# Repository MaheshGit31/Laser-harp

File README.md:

# Laser-harp

An 8-string laser harp. Break a laser beam, and it plays a note. it shows up as a usb midi device, so it works with any daw or synth on your laptop.

## how it works
 
8 red lasers on the base shine straight up at 8 phototransistors on a bar on top of them. when your hand breaks a beam, that string's signal flips and the esp32 sends a midi note over usb. a neopixel under each string lights up while you play it.

## frame idea
 
a wood or 3d-printed arch holds the bar, hollow curved side pillars carry the cable, and a chunky base case holds the base pcb. none of this is built yet.

## images

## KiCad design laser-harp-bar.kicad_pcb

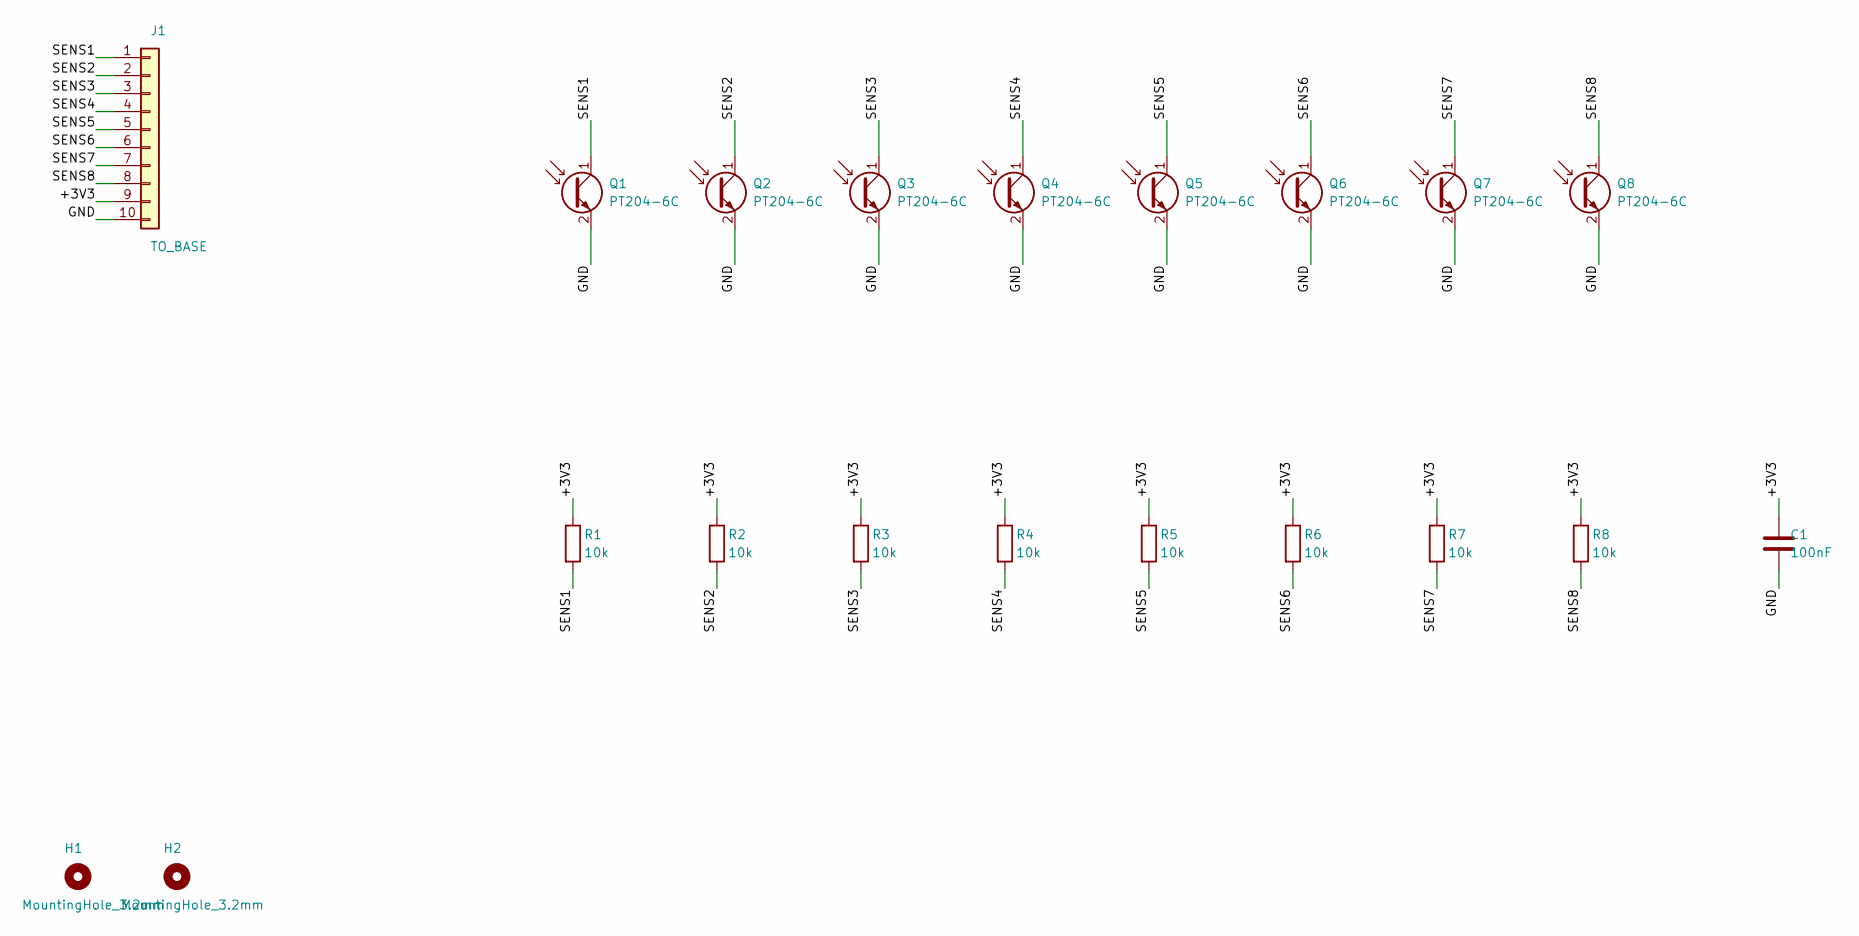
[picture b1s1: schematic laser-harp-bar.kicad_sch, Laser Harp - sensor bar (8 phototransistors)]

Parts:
C1: 100nF; C_0603_1608Metric
H1, H2: MountingHole_3.2mm; MountingHole_3.2mm_M3
J1: TO_BASE; PinHeader_1x10_P2.54mm_Vertical
Q1, Q2, Q3, Q4, Q5, Q6, Q7, Q8: PT204-6C; PT204-6C_D3.0mm
R1, R2, R3, R4, R5, R6, R7, R8: 10k; R_0603_1608Metric

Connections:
/+3V3: C1.1, J1.9, R1.1, R2.1, R3.1, R4.1, R5.1, R6.1, R7.1, R8.1
/GND: C1.2, J1.10, Q1.2 (E), Q2.2 (E), Q3.2 (E), Q4.2 (E), Q5.2 (E), Q6.2 (E), Q7.2 (E), Q8.2 (E)
/SENS1: J1.1, Q1.1 (C), R1.2
/SENS2: J1.2, Q2.1 (C), R2.2
/SENS3: J1.3, Q3.1 (C), R3.2
/SENS4: J1.4, Q4.1 (C), R4.2
/SENS5: J1.5, Q5.1 (C), R5.2
/SENS6: J1.6, Q6.1 (C), R6.2
/SENS7: J1.7, Q7.1 (C), R7.2
/SENS8: J1.8, Q8.1 (C), R8.2

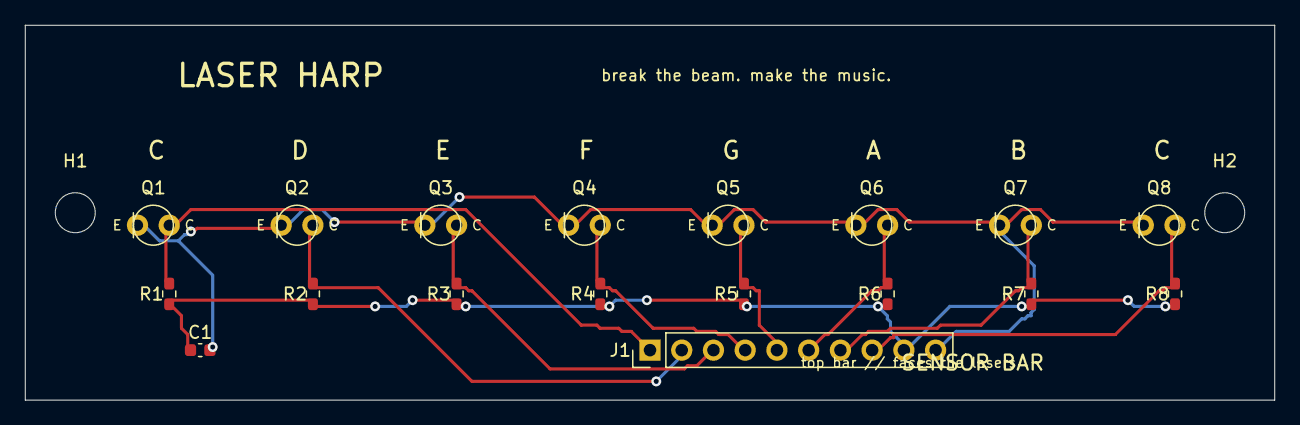
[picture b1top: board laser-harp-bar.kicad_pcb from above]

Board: 2 copper layers, 100.0 x 30.0 mm, 20 parts (0 on the bottom side), 10 nets.

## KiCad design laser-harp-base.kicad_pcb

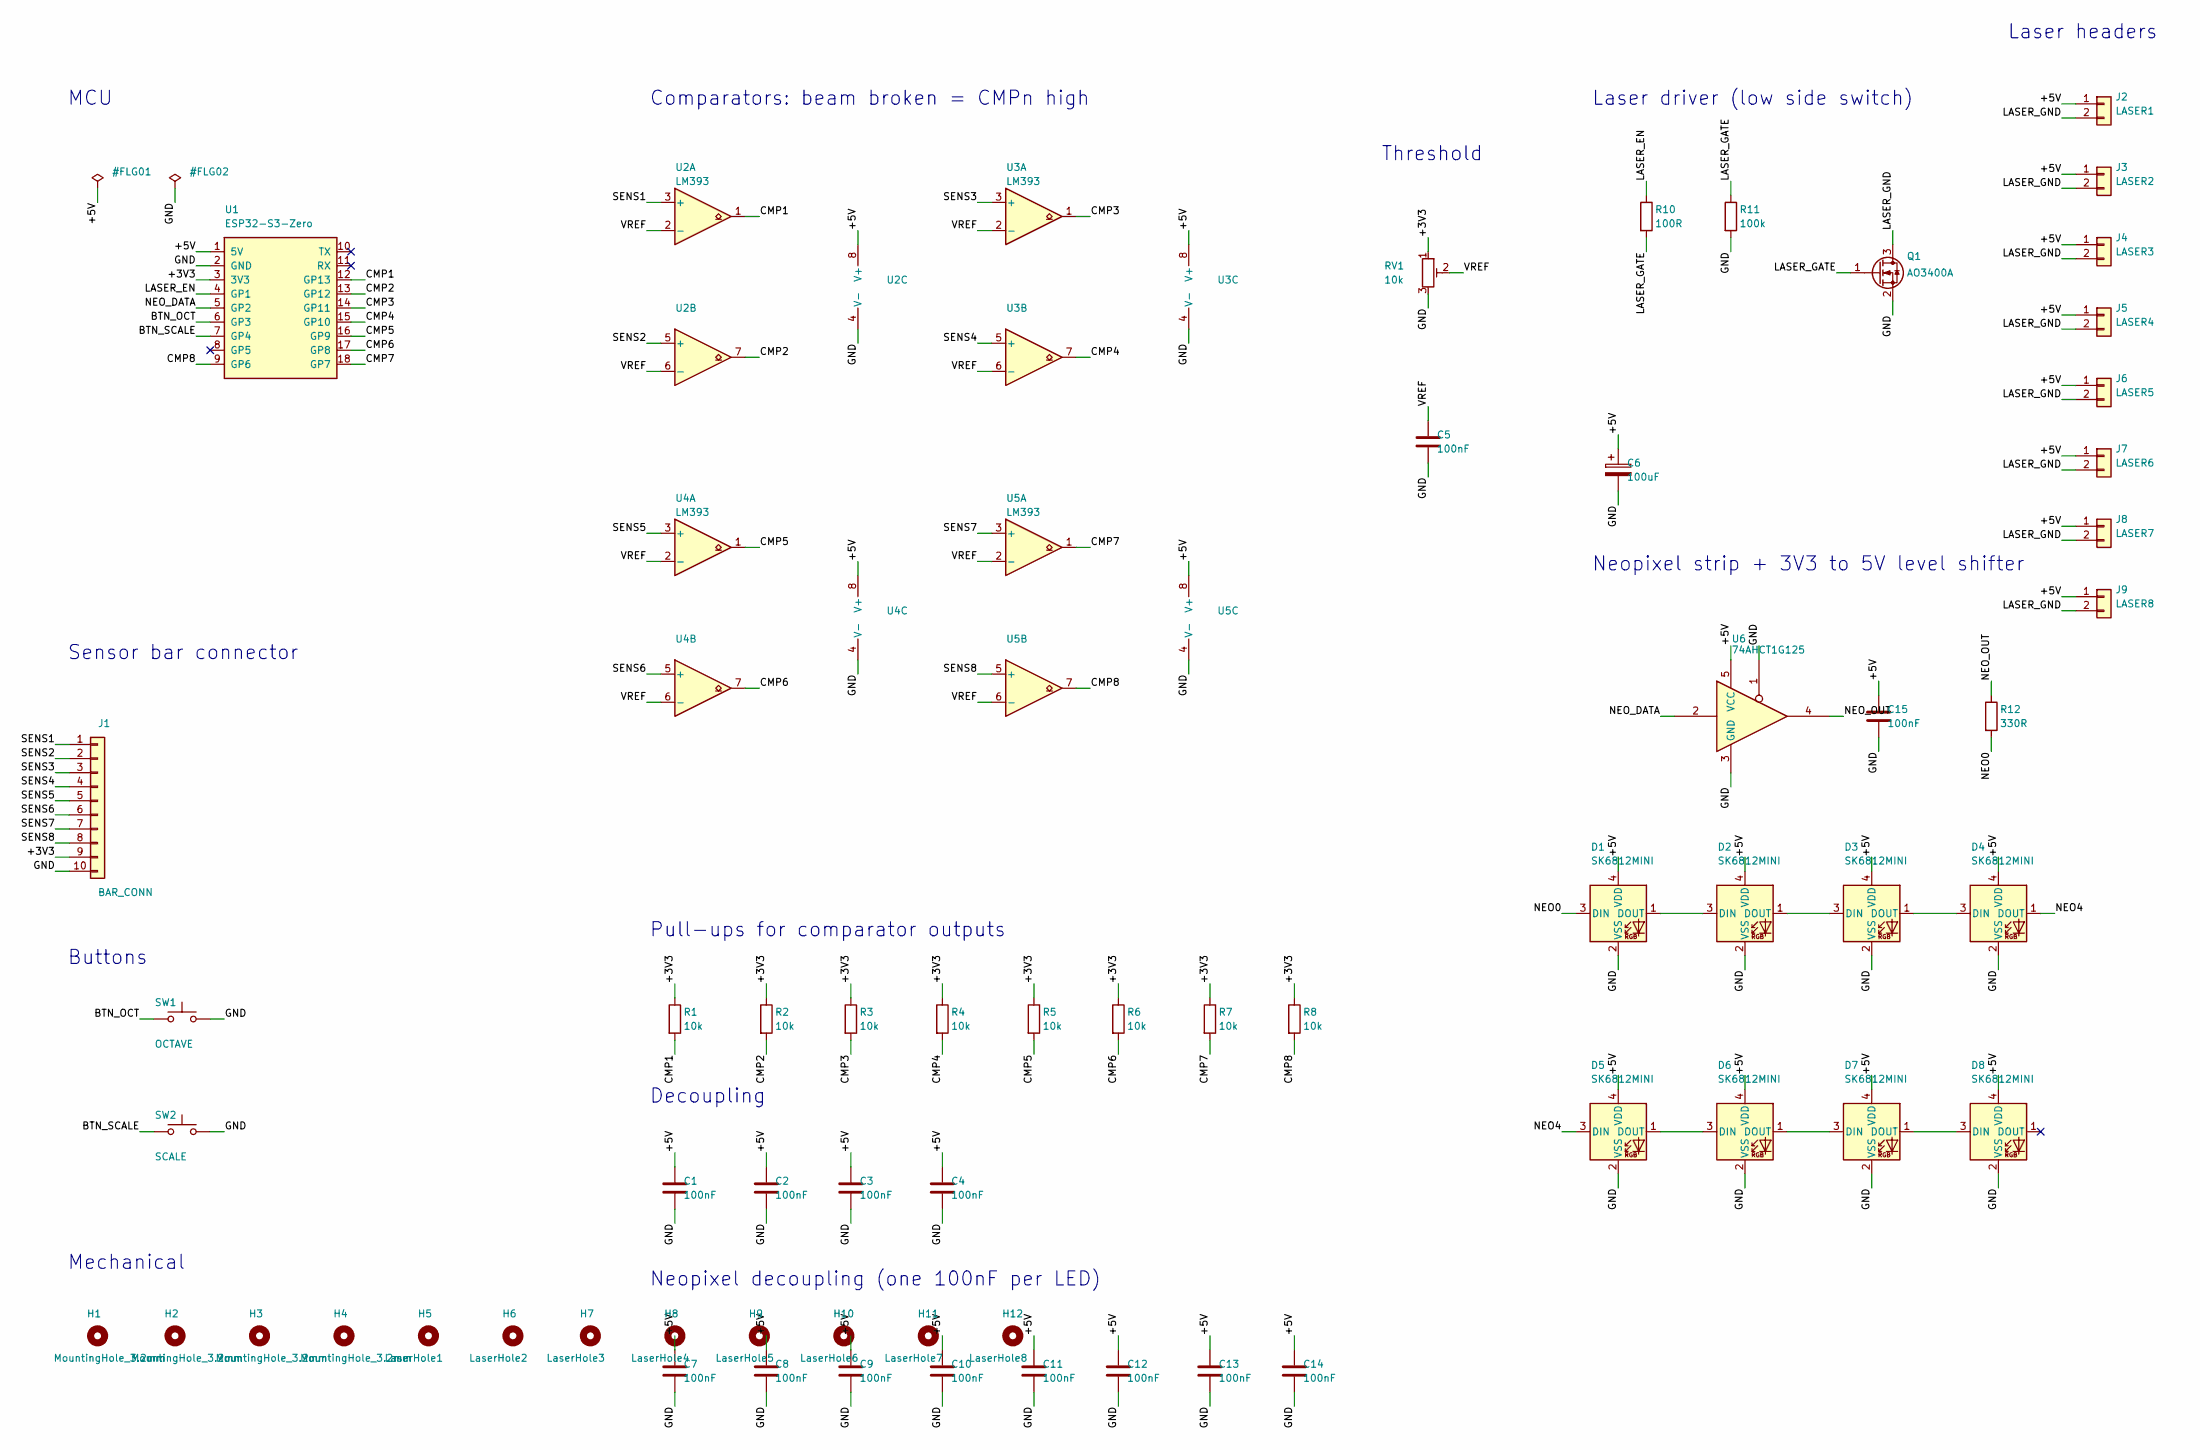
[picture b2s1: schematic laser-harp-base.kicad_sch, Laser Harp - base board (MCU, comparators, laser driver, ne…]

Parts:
C1, C2, C3, C4, C5, C7, C8, C9, C10, C11, C12, C13, C14, C15: 100nF; C_0603_1608Metric
C6: 100uF; CP_Elec_6.3x5.4
D1, D2, D3, D4, D5, D6, D7, D8: SK6812MINI; LED_SK6812MINI_PLCC4_3.5x3.5mm_P1.75mm
H1, H2, H3, H4: MountingHole_3.2mm; MountingHole_3.2mm_M3
H5: LaserHole1; MountingHole_6.4mm_M6
H6: LaserHole2; MountingHole_6.4mm_M6
H7: LaserHole3; MountingHole_6.4mm_M6
H8: LaserHole4; MountingHole_6.4mm_M6
H9: LaserHole5; MountingHole_6.4mm_M6
H10: LaserHole6; MountingHole_6.4mm_M6
H11: LaserHole7; MountingHole_6.4mm_M6
H12: LaserHole8; MountingHole_6.4mm_M6
J1: BAR_CONN; PinHeader_1x10_P2.54mm_Vertical
J2: LASER1; PinHeader_1x02_P2.54mm_Vertical
J3: LASER2; PinHeader_1x02_P2.54mm_Vertical
J4: LASER3; PinHeader_1x02_P2.54mm_Vertical
J5: LASER4; PinHeader_1x02_P2.54mm_Vertical
J6: LASER5; PinHeader_1x02_P2.54mm_Vertical
J7: LASER6; PinHeader_1x02_P2.54mm_Vertical
J8: LASER7; PinHeader_1x02_P2.54mm_Vertical
J9: LASER8; PinHeader_1x02_P2.54mm_Vertical
Q1: AO3400A; SOT-23
R1, R2, R3, R4, R5, R6, R7, R8: 10k; R_0603_1608Metric
R10: 100R; R_0603_1608Metric
R11: 100k; R_0603_1608Metric
R12: 330R; R_0603_1608Metric
RV1: 10k; Potentiometer_Bourns_3296W_Vertical
SW1: OCTAVE; SW_PUSH_6mm
SW2: SCALE; SW_PUSH_6mm
U1: ESP32-S3-Zero
U2, U3, U4, U5: LM393; SOIC-8_3.9x4.9mm_P1.27mm
U6: 74AHCT1G125; SOT-23-5

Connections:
/+3V3: J1.9, R1.1, R2.1, R3.1, R4.1, R5.1, R6.1, R7.1, R8.1, RV1.1, U1.3 (3V3)
/+5V: C1.1, C2.1, C3.1, C4.1, C6.1, C7.1, C8.1, C9.1, C10.1, C11.1, C12.1, C13.1, C14.1, C15.1, D1.4 (VDD), D2.4 (VDD), D3.4 (VDD), D4.4 (VDD), D5.4 (VDD), D6.4 (VDD), D7.4 (VDD), D8.4 (VDD), J2.1, J3.1, J4.1, J5.1, J6.1, J7.1, J8.1, J9.1, U1.1 (5V), U2.8 (V+), U3.8 (V+), U4.8 (V+), U5.8 (V+), U6.5 (VCC)
/BTN_OCT: SW1.1, U1.6 (GP3)
/BTN_SCALE: SW2.1, U1.7 (GP4)
/CMP1: R1.2, U1.12 (GP13), U2.1
/CMP2: R2.2, U1.13 (GP12), U2.7
/CMP3: R3.2, U1.14 (GP11), U3.1
/CMP4: R4.2, U1.15 (GP10), U3.7
/CMP5: R5.2, U1.16 (GP9), U4.1
/CMP6: R6.2, U1.17 (GP8), U4.7
/CMP7: R7.2, U1.18 (GP7), U5.1
/CMP8: R8.2, U1.9 (GP6), U5.7
/GND: C1.2, C2.2, C3.2, C4.2, C5.2, C6.2, C7.2, C8.2, C9.2, C10.2, C11.2, C12.2, C13.2, C14.2, C15.2, D1.2 (VSS), D2.2 (VSS), D3.2 (VSS), D4.2 (VSS), D5.2 (VSS), D6.2 (VSS), D7.2 (VSS), D8.2 (VSS), J1.10, Q1.2 (S), R11.2, RV1.3, SW1.2, SW2.2, U1.2 (GND), U2.4 (V-), U3.4 (V-), U4.4 (V-), U5.4 (V-), U6.1, U6.3 (GND)
/LASER_EN: R10.1, U1.4 (GP1)
/LASER_GATE: Q1.1 (G), R10.2, R11.1
/LASER_GND: J2.2, J3.2, J4.2, J5.2, J6.2, J7.2, J8.2, J9.2, Q1.3 (D)
/NEO0: D1.3 (DIN), R12.2
/NEO4: D4.1 (DOUT), D5.3 (DIN)
/NEO_DATA: U1.5 (GP2), U6.2
/NEO_OUT: R12.1, U6.4
/SENS1: J1.1, U2.3 (+)
/SENS2: J1.2, U2.5 (+)
/SENS3: J1.3, U3.3 (+)
/SENS4: J1.4, U3.5 (+)
/SENS5: J1.5, U4.3 (+)
/SENS6: J1.6, U4.5 (+)
/SENS7: J1.7, U5.3 (+)
/SENS8: J1.8, U5.5 (+)
/VREF: C5.1, RV1.2, U2.2 (-), U2.6 (-), U3.2 (-), U3.6 (-), U4.2 (-), U4.6 (-), U5.2 (-), U5.6 (-)
unnamed: D1.1 (DOUT), D2.3 (DIN)
unnamed: D2.1 (DOUT), D3.3 (DIN)
unnamed: D3.1 (DOUT), D4.3 (DIN)
unnamed: D5.1 (DOUT), D6.3 (DIN)
unnamed: D6.1 (DOUT), D7.3 (DIN)
unnamed: D7.1 (DOUT), D8.3 (DIN)

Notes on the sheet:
MCU
Sensor bar connector
Buttons
Comparators: beam broken = CMPn high
Threshold
Laser driver (low side switch)
Laser headers
Neopixel strip + 3V3 to 5V level shifter
Pull-ups for comparator outputs
Decoupling
Neopixel decoupling (one 100nF per LED)
Mechanical

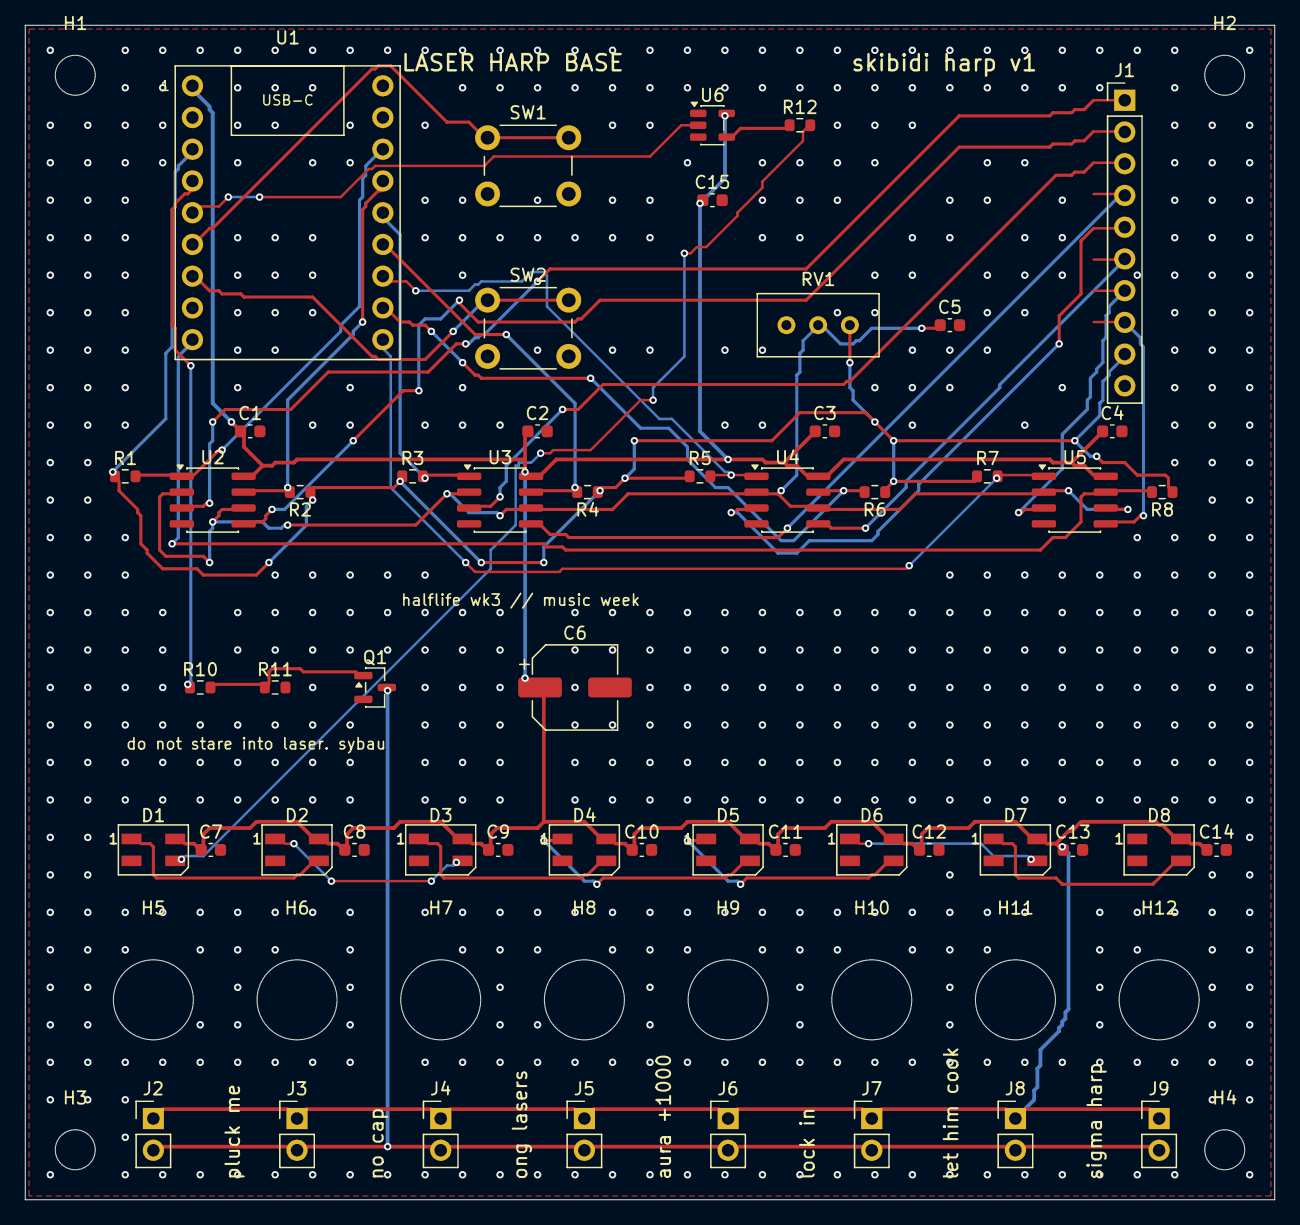
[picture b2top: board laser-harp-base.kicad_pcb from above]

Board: 2 copper layers, 100.0 x 94.0 mm, 65 parts (0 on the bottom side), 35 nets.
